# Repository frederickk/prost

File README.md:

# 🍻 Prost!

v.0.1.2

### Prost! uses Arduino Pro Micros as intermediary to allow Midi host to Midi host communication.

<sub>(Pros + Host) x 2 = [Prost!](https://dictionary.cambridge.org/dictionary/german-english/prost) SWDIT?</sub>

Here's a brief [demo video](https://www.youtube.com/watch?v=BwLtm9UBdX8) with [Ableton Live](https://www.ableton.com/), an [Organelle](https://www.critterandguitari.com/organelle), and [Norns/Fates](https://llllllll.co/t/fates-a-diy-norns-dac-board-for-raspberry-pi/). 

------
## 💾 Firmware

**Download**

```bash 
$ git clone https://github.com/frederickk/prost.git
```

**Dependencies**

Prost! requires 2 dependencies to build and upload. 

- Install [PlatformIO](https://platformio.org/platformio-ide) this is required to build and flash the Arduinos. You can either install the [CLI](https://platformio.org/install/cli) or the [IDE](https://platformio.org/platformio-ide).
- [USBMIDI](https://github.com/BlokasLabs/usbmidi/) is required for transmitting Midi data over USB, fortunately PlatformIO makes dependency bundling easy.

Before building and flashing be sure to install dependencies.

```bash
  # Install dependencies
  pio lib --storage-dir ./lib install 5841   
```

**Build and Flash**

For 5V / 16MHz boards use:

```bash
  # Build and flash firmware
  pio run -e sparkfun_promicro16 -t upload
```

If using 3.3V / 8MHz boards use:

```bash
  # Build and flash firmware
  pio run -e sparkfun_promicro8 -t upload
```

Be sure to flash both boards 😃.

------
## 🎛️ Hardware

Prost! uses 2 [Pro Micro](https://www.sparkfun.com/products/12587) boards (or any compatible board or clone with an [Atmel 32u4 chip](https://www.amazon.com/s?k=32U4&i=electronics&ref=nb_sb_noss_2)) connected serially (TX/RX) in order to pass USBMidi data. Other boards may work (e.g. Teensy), but I only tested with Pro Micros.

I've created a PCB which reduces the footprint of the device to be only slightly larger than a Pro Micro board itself (38mm x 35mm / 1.25" x 1.375"). Below I've soldered 2 header pins in order to test different boards, but you could solder the boards directly to further reduce the overall thickness (unless you opt to solder on the 3.5mm analog sync jack).

**Board**

A custom PCB is also available. if there's enough interest I would be willing to produce these in bulk and sell either bare PCB's or populated with components. For now you can order them yourself from [JLCPCB](https://jlcpcb.com/quote/gerberview/d1965d72-c9b5-4de7-8c59-df7167853c5e_1_0_6_0_0.html).

Although, the board is designed first and foremost for Pro Micros it can accomodate a number of other boards. Be mindful to align the marked `TX` and `RX` pins on the Prost! PCB with those on your board. 

| Board         | RX | TX | Voltage | Notes |
| ------------- | -- | -- | ------- | ----- |
| [Pro Micro](https://learn.sparkfun.com/tutorials/pro-micro--fio-v3-hookup-guide/hardware-overview-pro-micro) | 0  | 1  | 3.3 or 5 | |
| [Teensy 1.0, ++](https://www.pjrc.com/teensy/td_uart.html) | 2  | 3  | 3.3 or 5 | |
| [Teensy LC, 3.0, 3.1, 3.2, 3.5, 3.6, 4.0](https://www.pjrc.com/teensy/td_uart.html)  | 0  | 1  | 3.3 or 5 | |
| [Arduino Micro](https://content.arduino.cc/assets/Pinout-Micro_latest.pdf) | 20 | 21 | 3.3 or 5 | |
| [Adafruit Feather 32u4, Bluefruit](https://learn.adafruit.com/adafruit-feather-32u4-basic-proto/pinouts) | 0  | 1  | 3.3 | Board must be mounted upside down |
| [Adafruit ItsyBitsy 32u4](https://learn.adafruit.com/introducting-itsy-bitsy-32u4/pinouts) | 0  | 1  | 3 or 5 |

**BOM**

| Qty. | Part No. | Item |
| ---- | -------- | ---- |
| **2**    | | **5V/3.3V [Pro Micro](https://www.sparkfun.com/products/12587)** |
| **1**    | **[1825910-6](https://octopart.com/1825910-6-te+connectivity-42270338?r=sp)** | **6mm Momentary push button** |
| 2    | [WP154A4SUREQBFZGW](https://octopart.com/wp154a4sureqbfzgw-kingbright-12087875?r=sp) | 5mm RGB LED (optional) |
| 4    | | 1 x 10 female header (optional) |

Syncing with DIN Midi devices is also possible. Look for the 5-pin Midi graphic on the board and you'll find pin breakouts to connect a 5-pin Midi connector. Be sure to obtain 2 220 ohm resistors as well.

| Qty. | Part No. | Item |
| ---- | -------- | ---- |
| 1    | [1134](https://octopart.com/1134-adafruit+industries-32978196?r=sp) | 5-pin MIDI connector (optional) |
| 2    | [220R](https://octopart.com/search?q=220+ohm+resistor&currency=USD&specs=0&category_id=6312) | 220 ohm THT resistors (optional) |

Prost! also supports analog sync, which takes the USB Midi clock signal and converts it to 3.3V or 5V (depending on voltage of Pro Micro) pulse; for Volcas, Pocket Operators, etc. There's room on the board for an [SMD 3.5mm/.125" audio jack](https://octopart.com/search?q=CUI+SJ-3523-SMT&currency=USD&specs=0) or pads to solder a jack type of your choice.

| Qty. | Part No. | Item |
| ---- | -------- | ---- |
| 1    | [CUI SJ-3523-SMT](https://octopart.com/search?q=CUI+SJ-3523-SMT&currency=USD&specs=0) | SMD 3.54mm/.125" audio jack (optional) |

**Wiring**

The diagram below shows how to connect the the 2 Pro Micros TX and RX pins. A push button is wired to [reset the bootloader](https://learn.sparkfun.com/tutorials/pro-micro--fio-v3-hookup-guide/all#ts-reset) (for flashing if/as needed). The optional LEDs signal when Midi and Serial commands are being received and sent.

------
## 📜 License

[MIT](https://opensource.org/licenses/MIT)

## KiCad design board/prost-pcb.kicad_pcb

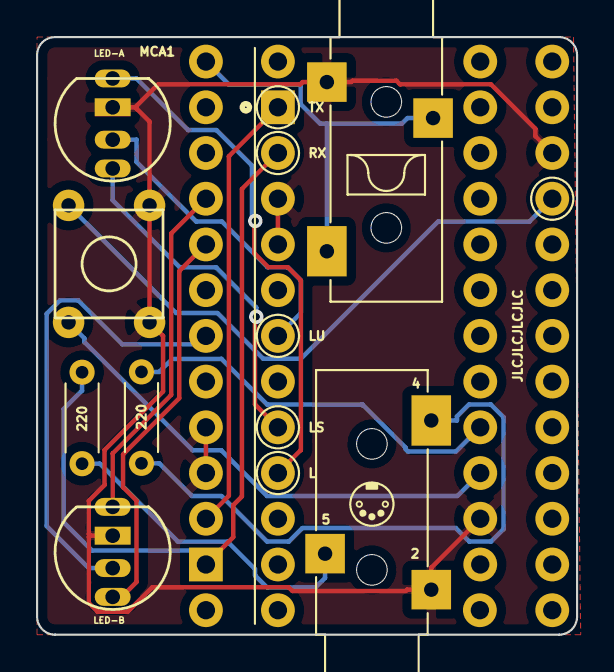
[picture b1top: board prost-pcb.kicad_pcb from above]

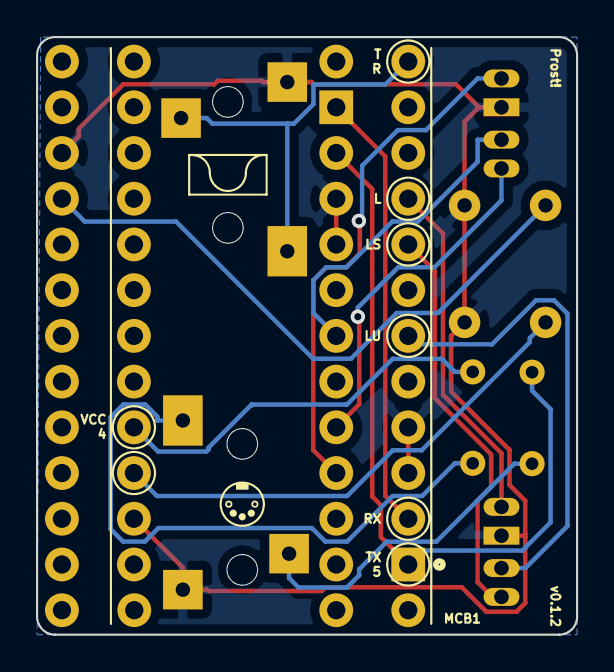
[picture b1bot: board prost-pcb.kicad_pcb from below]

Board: 2 copper layers, 30.0 x 33.2 mm, 13 parts (3 on the bottom side), 15 nets.

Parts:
D1, D2: LED_CRGB; LED_5MM_RGB
DRILL1: DRILL1
DRILL2: DRILL2
DRILL3: DRILL3
DRILL4: DRILL4
J1: MIDI-DIN-5; Jack_3.5mm_CUI_SJ-3523-SMT_Horizontal
J2: MONO 3.5mm AUDIO JACK; Jack_3.5mm_CUI_SJ-3523-SMT_Horizontal
MCA1: SPARKFUN_PRO_MICRO
MCB1: SPARKFUN_PRO_MICRO
R1, R2: 220; R_Axial_DIN0204_L3.6mm_D1.6mm_P5.08mm_Horizontal
S1: MOMENTARY_SWITCH_SPST; MINI_PUSHBUTTON_SWITCH

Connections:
GND: D1.1, D2.1, J1.S, J2.S, MCA1.3, MCA1.4, MCA1.23, MCB1.3, MCB1.4, MCB1.23, S1.3, S1.4
unnamed: D1.2, MCA1.9
unnamed: D1.3, MCA1.8
unnamed: D1.4, MCA1.6
unnamed: D2.2, MCB1.9
unnamed: D2.3, MCB1.8
unnamed: D2.4, MCB1.6
unnamed: J1.R, R2.1
unnamed: J1.T, R1.2
unnamed: J2.R, J2.T, MCB1.12
unnamed: MCA1.1, MCB1.2
unnamed: MCA1.2, MCB1.1, R2.2
unnamed: MCA1.22, S1.1
unnamed: MCB1.21, R1.1
unnamed: MCB1.22, S1.2

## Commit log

2020-06-01 Updated with PCB files, additional board support, and Midi DIN
    - Version bump 0.1.2
    - Added all board files required for reproduction (e.g. gerbers)
    - Added support for USB to analog sync
    - TODO support for Midi DIN-5 TRS
    - Added rudimentary support for non-Pro Micro 32u4 based boards
    - Updated README.md with additional documentation
